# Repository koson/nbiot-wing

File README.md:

# NBIoT Wing

This is a Feather "Wing" which can be added to any feather board. It works by sending AT commands over the RX/TX pins that are on D0/D1 of the feather board.

The NBIoT wing also has an optional USB port that allows it to be used as a stand-alone serial USB modem from your PC.

The wing features the BC66 modem by Quectel Wireless which features Cat NB1 LTE.

## Front

## Back

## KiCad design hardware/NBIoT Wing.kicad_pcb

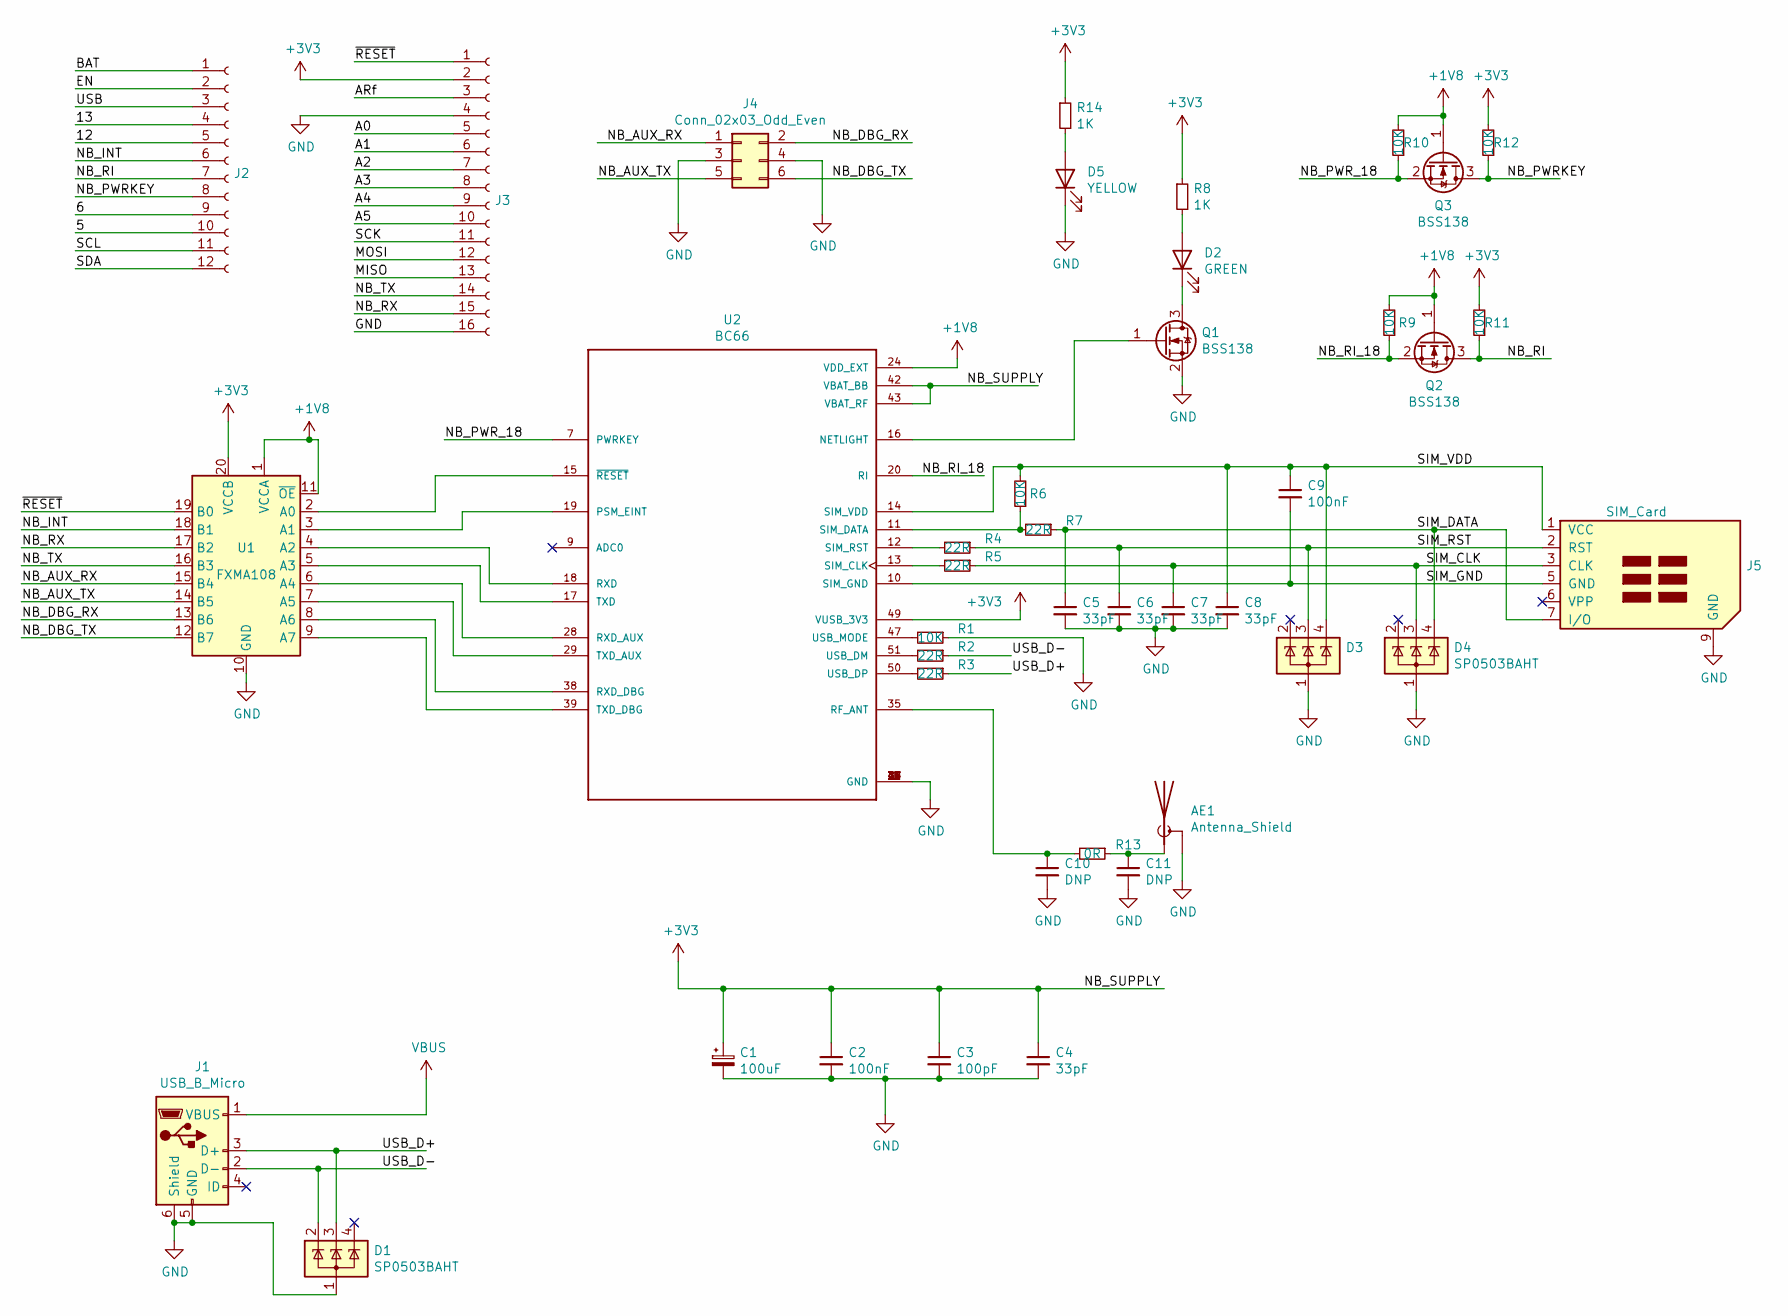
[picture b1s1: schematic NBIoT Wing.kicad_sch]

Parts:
AE1: Antenna_Shield; U.FL_Molex_MCRF_73412-0110_Vertical
C1: 100uF; CP_EIA-3528-12_Kemet-T
C2, C9: 100nF; C_0603_1608Metric
C3: 100pF; C_0603_1608Metric
C4, C5, C6, C7, C8: 33pF; C_0603_1608Metric
C10, C11: DNP; C_0603_1608Metric
D1, D3, D4: SP0503BAHT; SOT-143
D2: GREEN; LED_0603_1608Metric
D5: YELLOW; LED_0603_1608Metric
J1: USB_B_Micro; USB_Micro-B_Amphenol_10103594-0001LF_Horizontal
J2: Conn_01x12_Female; PinHeader_1x12_P2.54mm_Vertical
J3: Conn_01x16_Female; PinHeader_1x16_P2.54mm_Vertical
J4: Conn_02x03_Odd_Even; PinHeader_2x03_P2.54mm_Vertical
J5: SIM_Card; 0786463001
Q1, Q2, Q3: BSS138; SOT-23
R1, R6, R9, R10, R11, R12: 10K; R_0603_1608Metric
R2, R3, R4, R5, R7: 22R; R_0603_1608Metric
R8, R14: 1K; R_0603_1608Metric
R13: 0R; R_0603_1608Metric
U1: FXMA108; WQFN-20-1EP_2.5x4.5mm_P0.5mm_EP1x2.9mm
U2: BC66; XCVR_BC66

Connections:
+1V8: Q2.1 (G), Q3.1 (G), R9.2, R10.2, U1.1 (VCCA), U1.11 (~OE), U2.24 (VDD_EXT)
+3V3: C1.1, C2.1, C3.1, C4.1, J3.2, R8.1, R11.2, R12.2, R14.1, U1.20 (VCCB), U2.42 (VBAT_BB), U2.43 (VBAT_RF), U2.49 (VUSB_3V3)
/5: J2.10
/6: J2.9
/12: J2.5
/13: J2.4
/A0: J3.5
/A1: J3.6
/A2: J3.7
/A3: J3.8
/A4: J3.9
/A5: J3.10
/ARf: J3.3
/BAT: J2.1
/EN: J2.2
/MISO: J3.13
/MOSI: J3.12
/NB_AUX_RX: J4.1, U1.15 (B4)
/NB_AUX_TX: J4.5, U1.14 (B5)
/NB_DBG_RX: J4.2, U1.13 (B6)
/NB_DBG_TX: J4.6, U1.12 (B7)
/NB_INT: J2.6, U1.18 (B1)
/NB_PWRKEY: J2.8, Q3.3 (D), R12.1
/NB_PWR_18: Q3.2 (S), R10.1, U2.7 (PWRKEY)
/NB_RI: J2.7, Q2.3 (D), R11.1
/NB_RI_18: Q2.2 (S), R9.1, U2.20 (RI)
/NB_RX: J3.15, U1.17 (B2)
/NB_TX: J3.14, U1.16 (B3)
/SCK: J3.11
/SCL: J2.11
/SDA: J2.12
/SIM_CLK: C7.1, D4.3 (K), J5.3 (CLK), R5.1
/SIM_DATA: C5.1, D4.4 (K), J5.7 (I/O), R7.1
/SIM_GND: C9.2, J5.5 (GND), U2.10 (SIM_GND)
/SIM_RST: C6.1, D3.3 (K), J5.2 (RST), R4.1
/SIM_VDD: C8.1, C9.1, D3.4 (K), J5.1 (VCC), R6.2, U2.14 (SIM_VDD)
/USB: J2.3
/USB_D+: D1.3 (K), J1.3 (D+), R3.1
/USB_D-: D1.2 (K), J1.2 (D-), R2.1
/~RESET: J3.1, U1.19 (B0)
GND: AE1.2 (Shield), C1.2, C2.2, C3.2, C4.2, C5.2, C6.2, C7.2, C8.2, C10.2, C11.2, D1.1 (A), D3.1 (A), D4.1 (A), D5.1 (K), J1.5 (GND), J1.6 (Shield), J3.4, J3.16, J4.3, J4.4, J5.9 (GND), Q1.2 (S), R1.1, U1.10 (GND), U2.1 (GND), U2.27 (GND), U2.34 (GND), U2.36 (GND), U2.37 (GND), U2.40 (GND), U2.41 (GND)
unnamed: AE1.1 (A), C11.1, R13.1
unnamed: C10.1, R13.2, U2.35 (RF_ANT)
unnamed: D2.1 (K), Q1.3 (D)
unnamed: D2.2 (A), R8.2
unnamed: D5.2 (A), R14.2
unnamed: Q1.1 (G), U2.16 (NETLIGHT)
unnamed: R1.2, U2.47 (USB_MODE)
unnamed: R2.2, U2.51 (USB_DM)
unnamed: R3.2, U2.50 (USB_DP)
unnamed: R4.2, U2.12 (SIM_RST)
unnamed: R5.2, U2.13 (SIM_CLK)
unnamed: R6.1, R7.2, U2.11 (SIM_DATA)
unnamed: U1.2 (A0), U2.15 (~RESET)
unnamed: U1.3 (A1), U2.19 (PSM_EINT)
unnamed: U1.4 (A2), U2.18 (RXD)
unnamed: U1.5 (A3), U2.17 (TXD)
unnamed: U1.6 (A4), U2.28 (RXD_AUX)
unnamed: U1.7 (A5), U2.29 (TXD_AUX)
unnamed: U1.8 (A6), U2.38 (RXD_DBG)
unnamed: U1.9 (A7), U2.39 (TXD_DBG)
VBUS: J1.1 (VBUS)

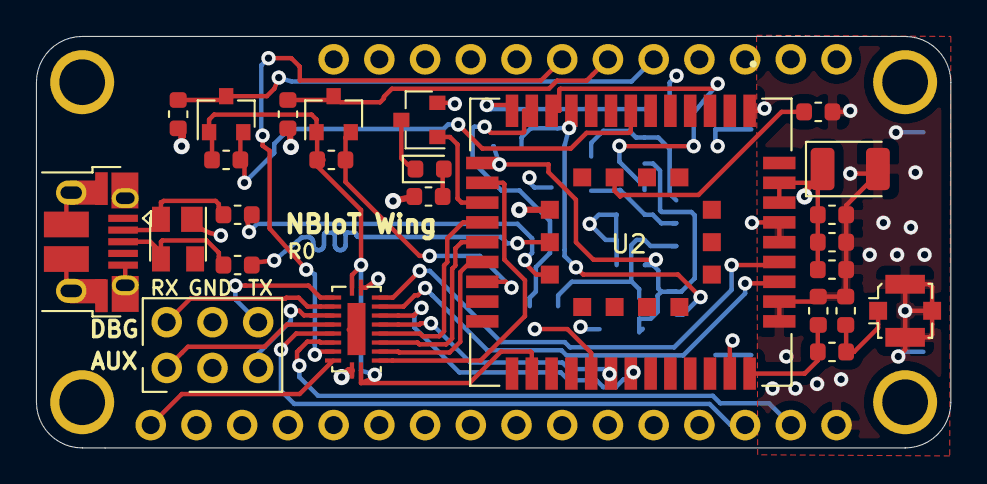
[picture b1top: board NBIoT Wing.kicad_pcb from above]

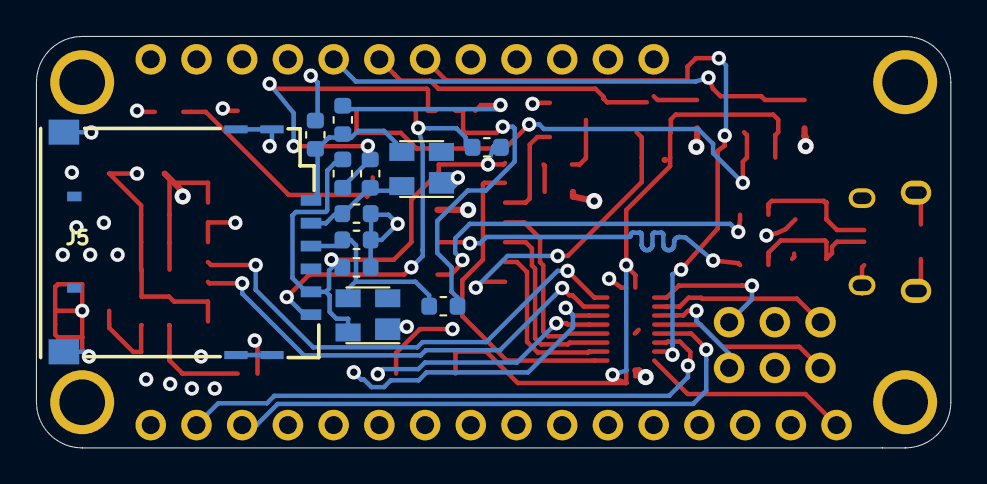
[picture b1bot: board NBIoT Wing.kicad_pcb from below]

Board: 4 copper layers, 50.8 x 22.9 mm, 40 parts (12 on the bottom side), 41 nets.

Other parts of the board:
PCB**: VAL**; PCB_FeatherWing

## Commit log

2019-12-25 initial
2019-12-29 BOM / gerbers
2024-04-09 kicad 8
